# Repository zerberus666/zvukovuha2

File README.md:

### Амбициозный проект невиданной доселе внешней звуковой платы на быстрых бескислородных электронах ###

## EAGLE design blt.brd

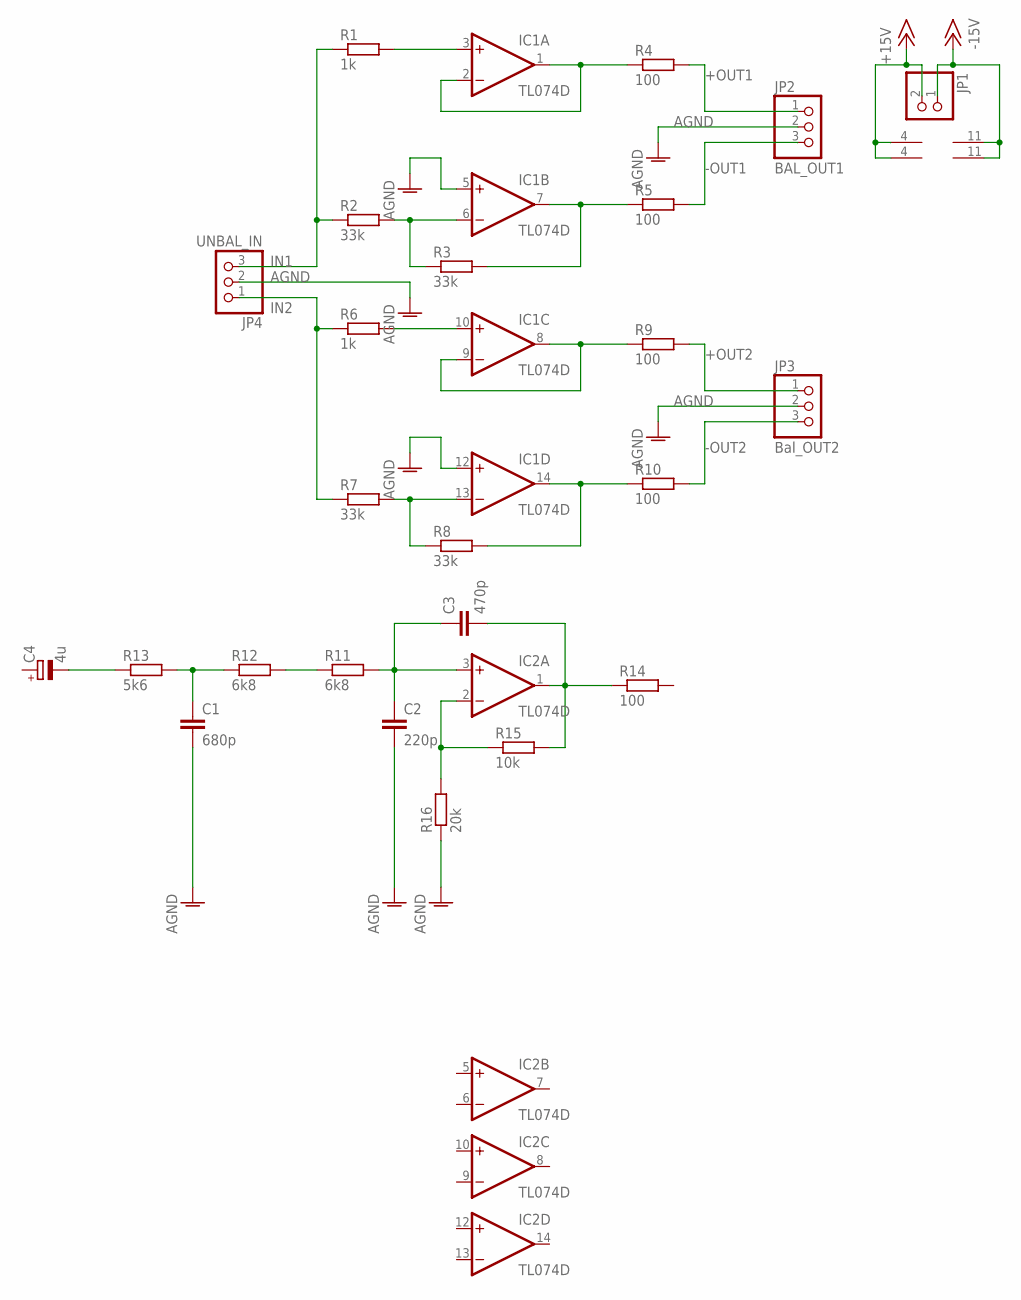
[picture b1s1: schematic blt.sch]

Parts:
C1: 680p; C1206
C2: 220p; C1206
C3: 470p; C1206
C4: 4u; UD-4X5,8_NICHICON
IC1, IC2: TL074D; SO14
JP1: PINHD-1X2; 1X02
JP2: BAL_OUT1; 1X03
JP3: Bal_OUT2; 1X03
JP4: UNBAL_IN; 1X03
R1, R6: 1k; R1206
R2, R3, R7, R8: 33k; R1206
R4, R5, R9, R10, R14: 100; R1206
R11, R12: 6k8; R1206
R13: 5k6; R1206
R15: 10k; R1206
R16: 20k; R1206

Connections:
+15V: IC1.4 (V+), IC2.4 (V+), JP1.2
+OUT1: JP2.1, R4.2
+OUT2: JP3.1, R9.2
-15V: IC1.11 (V-), IC2.11 (V-), JP1.1
-OUT1: JP2.3, R5.2
-OUT2: JP3.3, R10.2
AGND: C1.2, C2.2, IC1.5 (+IN), IC1.12 (+IN), JP2.2, JP3.2, JP4.2, R16.1
IN1: JP4.3, R1.1, R2.1
IN2: JP4.1, R6.1, R7.1
unnamed: IC1.3 (+IN), R1.2
unnamed: IC1.6 (-IN), R2.2, R3.1
unnamed: IC1.1 (OUT), IC1.2 (-IN), R4.1
unnamed: R11.1, R12.2
unnamed: C2.1, C3.1, IC2.3 (+IN), R11.2
unnamed: IC1.7 (OUT), R3.2, R5.1
unnamed: IC1.10 (+IN), R6.2
unnamed: IC1.8 (OUT), IC1.9 (-IN), R9.1
unnamed: C1.1, R12.1, R13.2
unnamed: IC1.13 (-IN), R7.2, R8.1
unnamed: IC1.14 (OUT), R8.2, R10.1
unnamed: C3.2, IC2.1 (OUT), R14.1, R15.2
unnamed: IC2.2 (-IN), R15.1, R16.2
unnamed: C4.-, R13.1

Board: 2 copper layers, 26 parts (11 on the bottom side), 23 nets, no tracks yet.

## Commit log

2015-01-21 second commit
2015-01-21 Shtucer test
2015-01-21 ещё один коммит
2015-01-26 ДОбавлена схема баллансного трансмитера
2015-01-26 некоторые новые обновления трансмитера
2015-01-27 temp
2015-03-04 дочертил схему фильтров
2015-03-04 дочертил схему фильтров2
2015-03-04 дочертил схему фильтров3
2015-03-04 дочертил схему фильтров4
2015-03-04 дочертил схему фильтров5
2015-03-04 дочертил схему фильтров6
2015-03-04 добавлен балансный приёмник
2015-03-11 Начал разработку блока питания
2015-03-12 блока питания продлжение
